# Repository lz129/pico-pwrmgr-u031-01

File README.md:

# Bluetooth LE based Remote Control Transmitter

What is it? A replacement for broken remote controls used for garage doors and similar purposes. Original equipment is often expensive or completely unobtainium.

## Versions

This document describes rev A. The design and the PCB have some [issues](ISSUES.md) which requires hardware patches on the PCB.

## Hardware

The major part is a [Raspberry Pi Pico W](https://pip-assets.raspberrypi.com/categories/686-raspberry-pi-pico-w/documents/RP-008312-DS-1-pico-w-datasheet.pdf) which is responsible to handle the Bluetooth LE protocol. In order to handle the low power mode of the device an additional microcontroller is used.

The board has been designed with Kicad 10. For details refer to 
[Schematic](bt-rc-tx/schematic.pdf), [PCB](bt-rc-tx/board.pdf), and [PCB-3d](bt-rc-tx/board-3d.png).

Fixes required on the PCB rev A:

* The decoupling capacitor C2 for the microcontroller shall be changed from 100n to 10u. 

* Parallel to C1 an additional electrolyte cap with 470u has to be connected.

* Pin 39 of the Raspberry Pi Pico W has to be disconnected from the +BATT network and a jumper Jx has to be added.

Modifications required on the Raspberry Pi Pico W board:

* Remove R2 and R10 ([power circuit Pico W](images/power-circuit-pico-w.png))

Refer to [images](images) for details.

|Image|Content|
|-----|--------|
|[Shipping box](images/shipping-box.jpg)|PCBs as delivered by JLCPCB|
|[Delivered boards](images/delivered-boards.jpg)|PCBs as delivered by JLCPCB|
|[Board unpopulated (front)](images/board-unpopulated-front.jpg)|The unpopulated PCB from the top side|
|[Board unpopulated (back)](images/board-unpopulated-back.jpg)|The unpopulated PCB from the back side|
|[Breadboard setup](images/breadboard-setup.jpg)|The complete design on a breadboard|
|[Debug connections (front)](images/debug-connections-front.jpg)|Populated PCB with debug connections (front)|
|[Debug connections (back)](images/debug-connections-back.jpg)|Populated PCB with debug connections (back)|
|[Board in housing](images/board-in-housing.jpg)|Populated PCB in housing|
|[Final device with batteries](images/final-device-open-box.jpg)|Final device with batteries and open housing|

## Software

### Power Controller

The power controller, a STM32U031 microcontroller handles power up and power down of the Raspberry Pi Pico W, reads keyboard input and controls the LEDs. When completely powered down the transmitter draws only approx. 400nA from the Batteries.

The power controller shuts down the Raspi automatically after a given time (currently 10s) in case the Python script does not complete for whatever reason. The script is able to send a signal over GPIO to the power controller to request an immediate shutdown after its job has finished.

To assist development the power controller can be switched to a debug mode where the Raspberry Pi is powered without timeout. This mode shall be used for Python script development. The mode can be activated by pressing button A for more than 3s. Press button A again to leave the debug mode.

Another debug and test aid is the inhibit power down jumper J4. When active the power controller does not go into power down mode but behaves otherwise identical. Use this jumper when debugging the power controller with ST-Link.

__Note:__ Powering the Raspberry Pi Pico W without timeout is only possible when the jumper J4 is set.

__IMPORTANT:__ The jumper J5 (currently not in rev A design) MUST be removed when connecting the Raspberry Pi Pico W via USB cable to a PC. The cable would supply the power controller with the USB bus voltage of 5V. The power controller however is a 3.3V device which can be damaged in this mode. Instead connect the battery or a lab power supply with 3.3V to supply the power controller.

### Raspberry Pi Pico W

Timing and performance is not critical in the application. Therefore a solution with [Micropython](https://micropython.org) has been chosen. Prebuilt versions for the Raspberry Pi Pico W are available [here](https://micropython.org/download/RPI_PICO_W/). Installation of the Python system can be easily done without tools unsing the UF2 bootloader.

The current python [script](python/garagedoor_central.py) is minimalistic at this time and can be extended as necessary to add additional features.

__Attention__: The sample script has no means for secure communication!

### Connectors and Jumpers

All connectors and jumpers are located on the back side of the PCB.

__J1__ is the connector for the battery. The transmitter is designed to operate on two AA or AAA cells. Both alkali mangan and NiMH cells can be used. Note that the voltage range is dicated by the microcontroller which operates on 1.71 to 3.6 volts and the buck/boost converter in the Raspberry Pi Pico W module which accepts 1.8 to 5.5 volts. Therefore the effective voltage range is between 1.8 and 3.6 volts.

__J3__ is a debug connector to attach a debug probe like the ST-Link from ST Microelectronics. The pin assignment is as follows:

|Pin|Purpose|Comments|
|---|-------|--------|
|1|GND|
|2|VCC|This is a sense wire for the debug probe to handle the voltage levels correctly. Do not provide power on this pin!|
|3|SWDIO|Serial Wire Debug data I/O 
|4|SWCLK|Serial Wire Debug clock
|5|/Reset|Reset controller

__J5__ jumper to inhibit shutdown. Use it when debugging to avoid debug probe disconnect due to powering down the chip. For normal operation and low power while not using the device the jumper has to be removed.

__Jx__ jumper patched into the rev A design. It disconnects the incoming power from the USB to the microcontroller. __The microcontroller can be damaged when an USB cable is connected to the Raspberry Pi board and the jumper is not removed.__

# BOM

|Reference|Qty|Value|DNP|Exclude from BOM|Exclude from Board|Footprint|Datasheet|
|---------|---|-----|---|----------------|------------------|------|----|
|A1|1|RaspberryPi_Pico_W||||Module:RaspberryPi_Pico_W_SMD_HandSolder|https://datasheets.raspberrypi.com/picow/pico-w-datasheet.pdf|
|C1|1|47u||||Capacitor_SMD:C_1206_3216Metric|
|C2|1|100n||||Capacitor_SMD:C_0805_2012Metric|
|D3|1|LED1||||LED_THT:LED_D5.0mm|
|D4|1|LED2||||LED_THT:LED_D5.0mm|
|J1|1|Battery 3V||||Connector_PinHeader_2.54mm:PinHeader_1x02_P2.54mm_Horizontal|
|J3|1|SW Debug||||Connector_PinHeader_2.54mm:PinHeader_1x05_P2.54mm_Horizontal|
|J4|1|Inhibit Shutdown||||Connector_PinHeader_2.54mm:PinHeader_1x02_P2.54mm_Horizontal|
|R4,R5|2|2k2||||Resistor_SMD:R_0805_2012Metric|
|SW2|1|BUTTON1||||Button_Switch_THT:SW_PUSH_6mm|
|SW3|1|BUTTON2||||Button_Switch_THT:SW_PUSH_6mm|
|U2|1|STM32U031F8Px||||Package_SO:TSSOP-20_4.4x6.5mm_P0.65mm|https://www.st.com/resource/en/datasheet/stm32u031f8.pdf|
||1|STRAPUBOX 6062 GR Plastic Box 85x65x28mm|||x|Housing|
|Cx|1|470u||||Aluminium Elko radial|

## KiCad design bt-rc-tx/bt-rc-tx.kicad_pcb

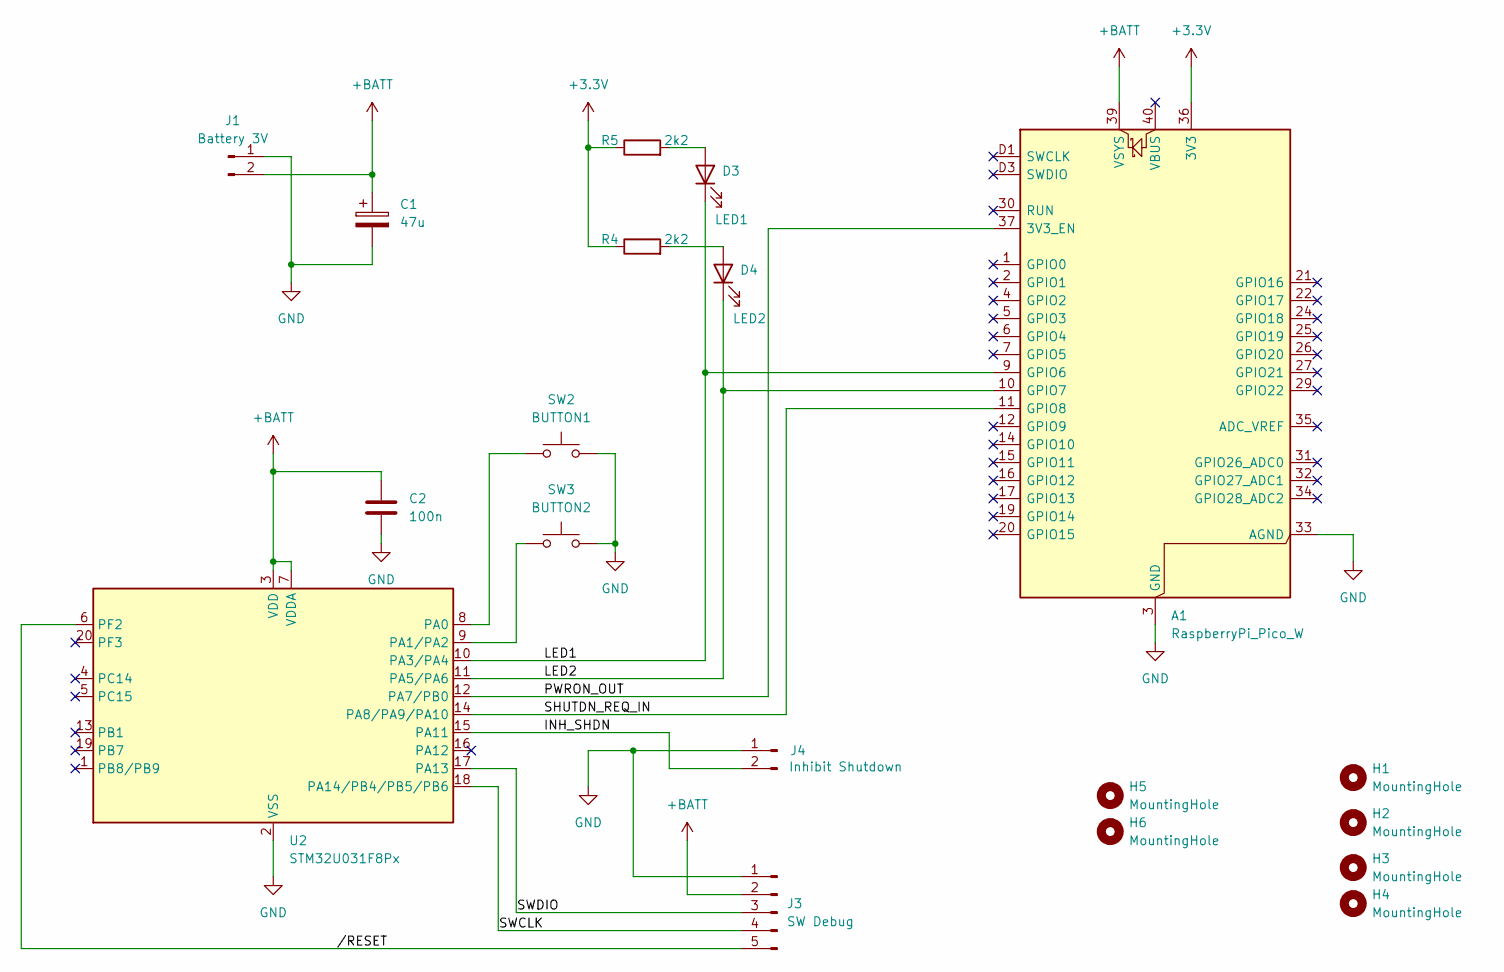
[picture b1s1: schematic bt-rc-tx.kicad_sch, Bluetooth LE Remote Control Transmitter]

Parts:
A1: RaspberryPi_Pico_W; RaspberryPi_Pico_W_SMD_HandSolder
C1: 47u; C_1206_3216Metric
C2: 100n; C_0805_2012Metric
D3: LED1; LED_D5.0mm
D4: LED2; LED_D5.0mm
H1, H2, H3, H4, H5, H6: MountingHole; MountingHole_2.5mm
J1: Battery 3V; PinHeader_1x02_P2.54mm_Horizontal
J3: SW Debug; PinHeader_1x05_P2.54mm_Horizontal
J4: Inhibit Shutdown; PinHeader_1x02_P2.54mm_Horizontal
R4, R5: 2k2; R_0805_2012Metric
SW2: BUTTON1; SW_PUSH_6mm
SW3: BUTTON2; SW_PUSH_6mm
U2: STM32U031F8Px; TSSOP-20_4.4x6.5mm_P0.65mm

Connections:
+3.3V: A1.36 (3V3), R4.1, R5.1
+BATT: A1.39 (VSYS), C1.1, C2.1, J1.2, J3.2, U2.3 (VDD), U2.7 (VDDA)
/INH_SHDN: J4.2, U2.15 (PA11)
/LED1: A1.9 (GPIO6), D3.1 (K), U2.10 (PA3/PA4)
/LED2: A1.10 (GPIO7), D4.1 (K), U2.11 (PA5/PA6)
/PWRON_OUT: A1.37 (3V3_EN), U2.12 (PA7/PB0)
/SHUTDN_REQ_IN: A1.11 (GPIO8), U2.14 (PA8/PA9/PA10)
/SWCLK: J3.4, U2.18 (PA14/PB4/PB5/PB6)
/SWDIO: J3.3, U2.17 (PA13)
//RESET: J3.5, U2.6 (PF2)
GND: A1.3 (GND), A1.8 (GND), A1.13 (GND), A1.18 (GND), A1.23 (GND), A1.28 (GND), A1.33 (AGND), A1.38 (GND), A1.D2 (GND), C1.2, C2.2, J1.1, J3.1, J4.1, SW2.2, SW3.2, U2.2 (VSS)
unnamed: D3.2 (A), R5.2
unnamed: D4.2 (A), R4.2
unnamed: SW2.1, U2.8 (PA0)
unnamed: SW3.1, U2.9 (PA1/PA2)

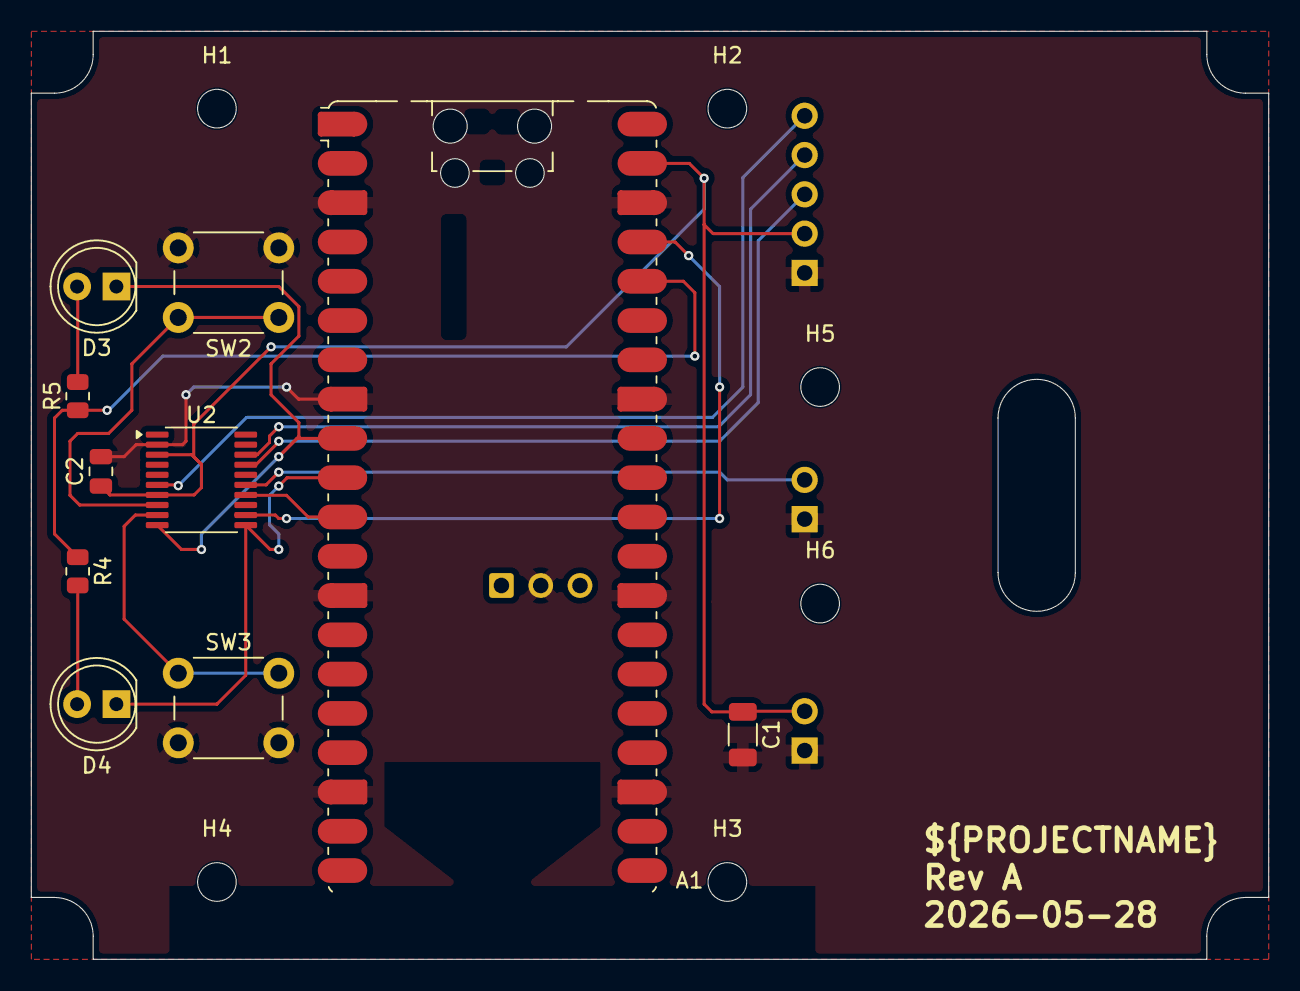
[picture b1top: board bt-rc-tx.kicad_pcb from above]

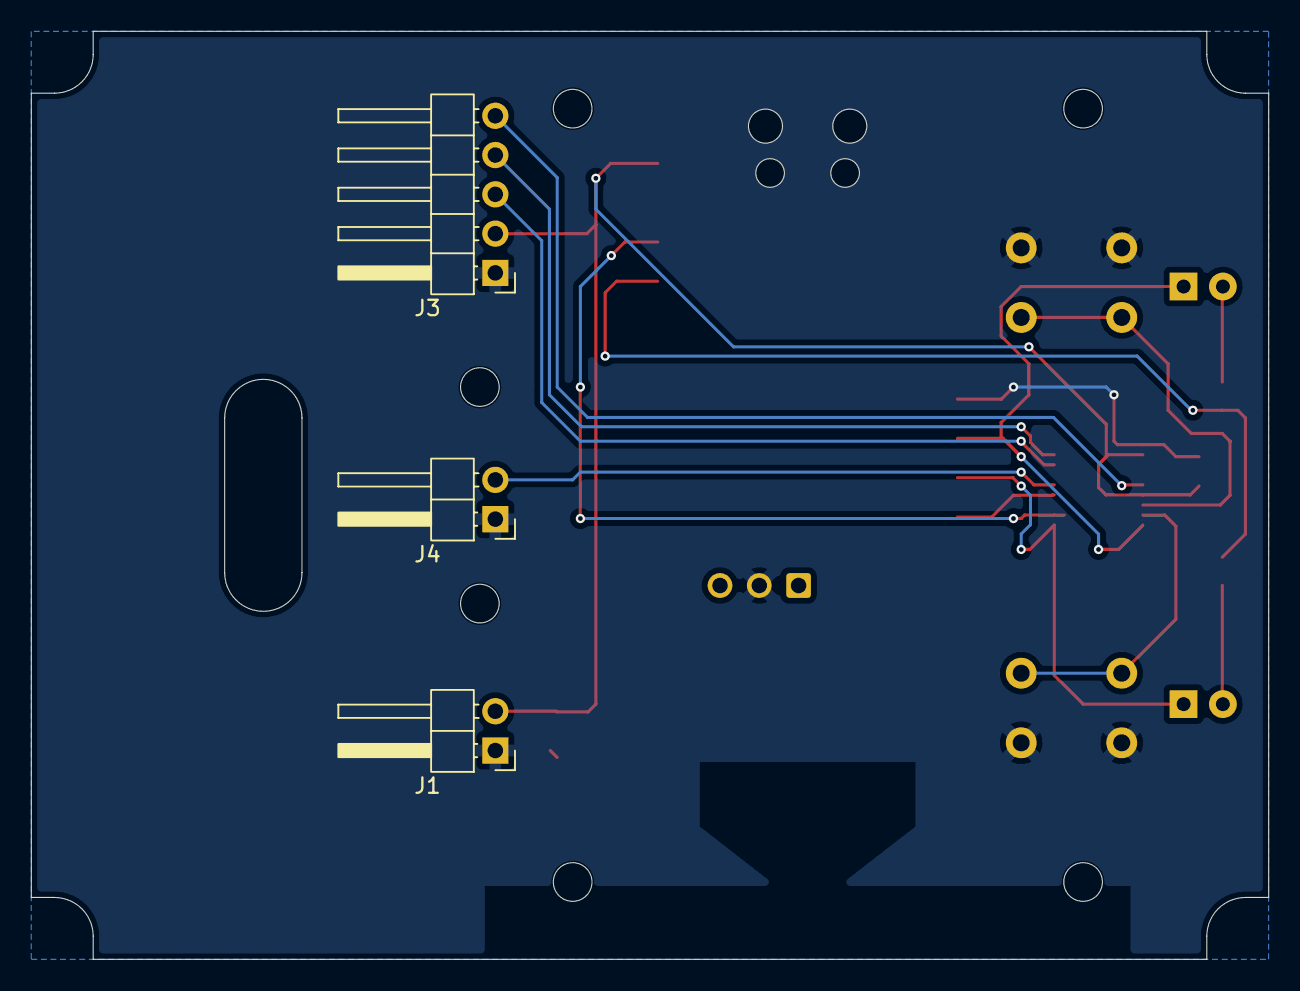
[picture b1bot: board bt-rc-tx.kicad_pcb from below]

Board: 2 copper layers, 80.0 x 60.0 mm, 19 parts (3 on the bottom side), 15 nets.

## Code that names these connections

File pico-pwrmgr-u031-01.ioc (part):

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Mcu.Name=STM32U031F8Px
Mcu.Package=TSSOP20
Mcu.UserName=STM32U031F8Px
PA0-CK_IN.GPIOParameters=GPIO_PuPd,GPIO_Label
PA0-CK_IN.GPIO_Label=BUTTON1
PA0-CK_IN.GPIO_PuPd=GPIO_PULLUP
PA0-CK_IN.Signal=GPIO_Input
PA1.GPIOParameters=GPIO_PuPd,GPIO_Label
PA1.GPIO_Label=BUTTON2
PA1.GPIO_PuPd=GPIO_PULLUP
PA1.Signal=GPIO_Input
PA11\ [PA9].GPIOParameters=GPIO_PuPd,GPIO_Label
PA11\ [PA9].GPIO_Label=INH_SHDN
PA11\ [PA9].GPIO_PuPd=GPIO_PULLUP
PA11\ [PA9].Signal=GPIO_Input
PA13\ (SWDIO).Mode=Serial_Wire
PA13\ (SWDIO).Signal=DEBUG_JTMS-SWDIO
PA14\ (SWCLK).Mode=Serial_Wire
PA14\ (SWCLK).Signal=DEBUG_JTCK-SWCLK
PA14\ (SWCLK)__PB4__PB5__PB6.StandardMode=true
PA1__PA2.StandardMode=true
PA3.GPIOParameters=PinState,GPIO_PuPd,GPIO_Label,GPIO_ModeDefaultOutputPP
PA3.GPIO_Label=LED1
PA3.GPIO_ModeDefaultOutputPP=GPIO_MODE_OUTPUT_OD
PA3.GPIO_PuPd=GPIO_NOPULL
PA3.PinState=GPIO_PIN_SET
PA3.Signal=GPIO_Output
PA3__PA4.StandardMode=true
PA5.GPIOParameters=PinState,GPIO_PuPd,GPIO_Label,GPIO_ModeDefaultOutputPP
PA5.GPIO_Label=LED2
PA5.GPIO_ModeDefaultOutputPP=GPIO_MODE_OUTPUT_OD
PA5.GPIO_PuPd=GPIO_NOPULL
PA5.PinState=GPIO_PIN_SET
PA5.Signal=GPIO_Output
PA5__PA6.StandardMode=true
PA7.GPIOParameters=GPIO_Label
PA7.GPIO_Label=PWRON_OUT
PA7.Signal=GPIO_Output
PA7__PB0.StandardMode=true
PA8.GPIOParameters=GPIO_PuPd,GPIO_Label
PA8.GPIO_Label=SHUTDN_REQ_IN
PA8.GPIO_PuPd=GPIO_PULLUP
PA8.Signal=GPIO_Input
PB8__PB9.StandardMode=true
RCC.HSE_VALUE=4000000
RCC.SYSCLKFreq_VALUE=4000000
RCC.SYSCLKSource=RCC_SYSCLKSOURCE_MSI
board=custom

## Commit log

2026-05-16 init
2026-05-16 fixes
2026-05-28 Add project title and PCB image to README
